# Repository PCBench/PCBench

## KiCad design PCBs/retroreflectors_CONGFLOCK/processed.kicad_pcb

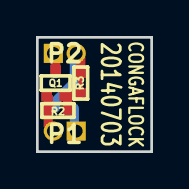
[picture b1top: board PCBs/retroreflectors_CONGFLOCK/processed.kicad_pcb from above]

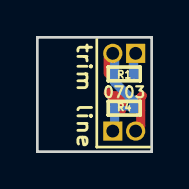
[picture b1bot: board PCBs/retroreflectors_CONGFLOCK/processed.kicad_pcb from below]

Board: 2 copper layers, 6.3 x 6.4 mm, 7 parts (2 on the bottom side), 5 nets.

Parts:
P1: INPUT; GSG-50MIL-HEADER-1x2-TH
P2: ANTENNA; GSG-50MIL-HEADER-1x2-TH
Q1: MOSFET_N; GSG-SOT416-GDS
R1: DNP; GSG-0402
R2: 100k; GSG-0402
R3, R4: 0; GSG-0402-SHORT-10MIL

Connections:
/DRAIN: P2.1, Q1.D, R1.1
/GATE: P1.2, Q1.G, R2.1
/SOURCE: Q1.S, R2.2, R3.2
GND: P2.2, R1.2, R3.1, R4.1
unnamed: P1.1, R4.2

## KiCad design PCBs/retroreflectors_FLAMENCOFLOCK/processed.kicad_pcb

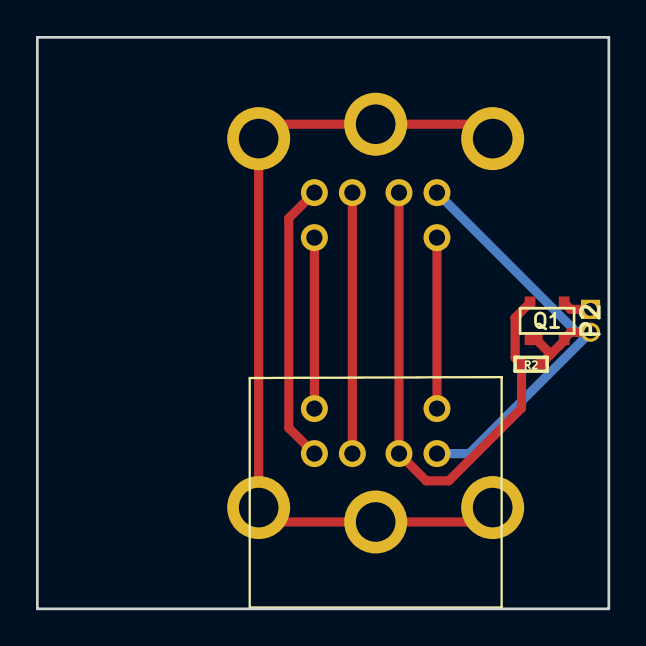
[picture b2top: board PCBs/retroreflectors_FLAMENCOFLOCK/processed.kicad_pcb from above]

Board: 2 copper layers, 31.8 x 31.8 mm, 5 parts (1 on the bottom side), 8 nets.

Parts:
J1, J2: MINIDIN6; GSG-MD-6006
P2: ANTENNA; GSG-50MIL-HEADER-1x2-TH
Q1: MOSFET_N; GSG-SOT143B-GDS
R2: 10k; GSG-0402

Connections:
/DRAIN: P2.1, Q1.D
/GATE: J1.1, J2.1, Q1.G, R2.1
/SHIELD: J1.0, J2.0
GND: J1.3, J2.3, P2.2, Q1.B, Q1.S, R2.2
unnamed: J1.2, J2.2
unnamed: J1.5, J2.5
unnamed: J1.4, J2.4
unnamed: J1.6, J2.6

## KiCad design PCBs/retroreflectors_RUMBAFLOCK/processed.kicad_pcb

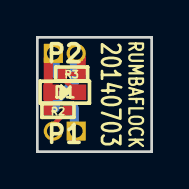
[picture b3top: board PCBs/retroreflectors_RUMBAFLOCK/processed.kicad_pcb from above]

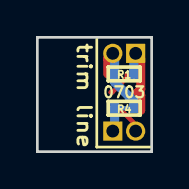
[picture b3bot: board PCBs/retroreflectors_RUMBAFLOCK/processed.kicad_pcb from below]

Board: 2 copper layers, 6.3 x 6.4 mm, 7 parts (2 on the bottom side), 5 nets.

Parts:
D1: PIN; GSG-0603D
P1: INPUT; GSG-50MIL-HEADER-1x2-TH
P2: ANTENNA; GSG-50MIL-HEADER-1x2-TH
R1: DNP; GSG-0402
R2: 10k; GSG-0402
R3, R4: 0; GSG-0402-SHORT-10MIL

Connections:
GND: P2.2, R1.2, R3.1, R4.1
unnamed: P1.1, R4.2
unnamed: P1.2, R2.1
unnamed: D1.2, R3.2
unnamed: D1.1, P2.1, R1.1, R2.2

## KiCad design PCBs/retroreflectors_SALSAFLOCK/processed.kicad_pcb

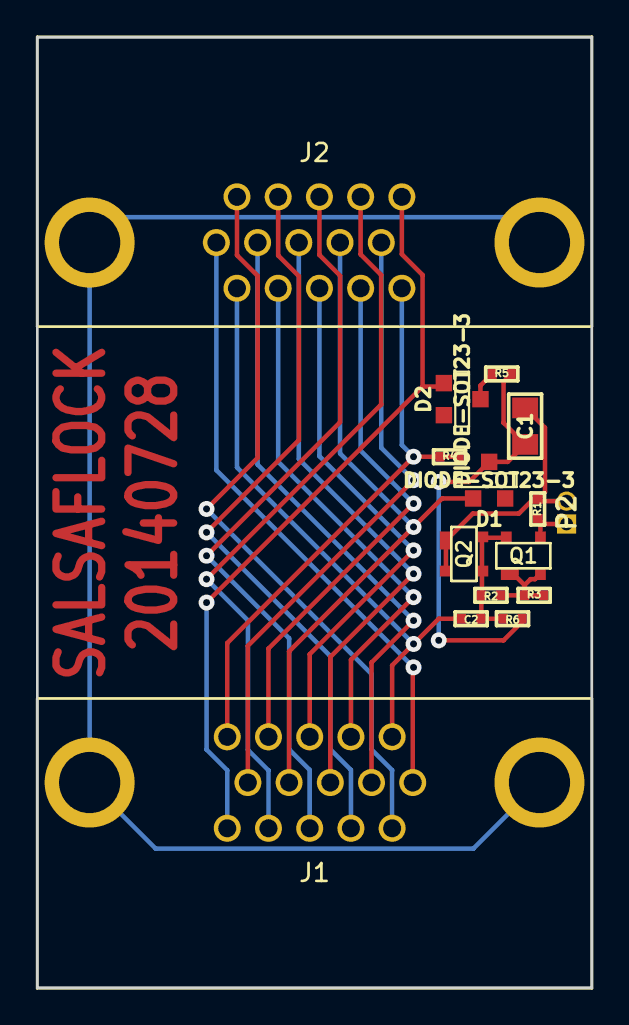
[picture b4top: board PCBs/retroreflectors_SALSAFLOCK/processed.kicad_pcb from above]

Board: 2 copper layers, 30.8 x 52.8 mm, 15 parts (0 on the bottom side), 22 nets.

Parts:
C1: 22uF; GSG-0805
C2: 1uF; GSG-0402
D1, D2: DIODE-SOT23-3; GSG-SOT23-3
J1, J2: DB15-VGA; GSG-DB15-VGA
P2: ANTENNA; GSG-50MIL-HEADER-1x2-TH
Q1, Q2: MOSFET_N; GSG-SOT143B-GDS
R1: DNP; GSG-0402
R2, R5, R6: 10k; GSG-0402
R3, R4: 0; GSG-0402-SHORT-10MIL

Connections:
/DRAIN: P2.1, Q1.D, R1.1
/GATE: C2.2, Q1.G, Q2.D, Q2.G, R2.1, R6.1
/KEY: D1.1, J1.9, J2.9
/RED: C2.1, J1.1, J2.1
/SCL: D2.1, J1.15, J2.15
/SHIELD: J1.0, J2.0
/SOURCE: Q1.B, Q1.S, R2.2, R3.2
/VGAGND: J1.5, J2.5, R4.2
GND: C1.1, P2.2, Q2.B, Q2.S, R1.2
unnamed: J1.10, J2.10
unnamed: J1.7, J2.7
unnamed: J1.2, J2.2
unnamed: J1.3, J2.3
unnamed: J1.4, J2.4
unnamed: J1.6, J2.6
unnamed: J1.8, J2.8
unnamed: J1.11, J2.11
unnamed: J1.12, J2.12
unnamed: J1.13, J2.13
unnamed: J1.14, J2.14
unnamed: D2.3, R5.2
unnamed: C1.2, D1.3, R5.1, R6.2

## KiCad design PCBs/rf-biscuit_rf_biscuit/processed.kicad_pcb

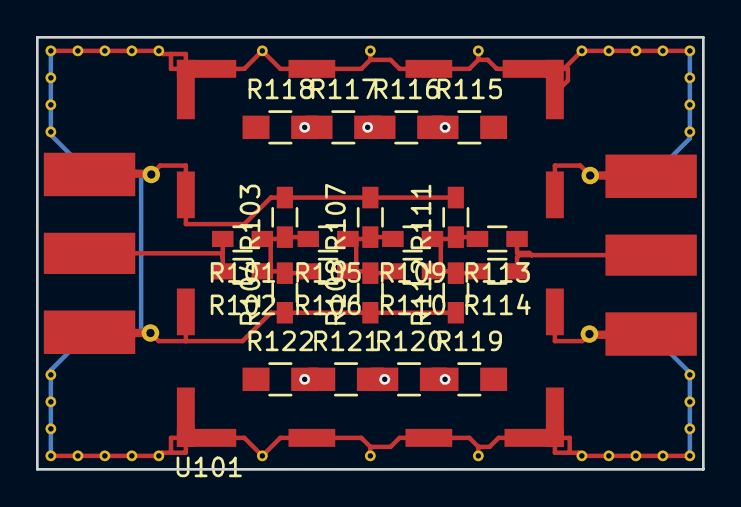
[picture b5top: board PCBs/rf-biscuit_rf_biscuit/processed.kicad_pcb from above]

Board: 2 copper layers, 37.0 x 24.0 mm, 25 parts (0 on the bottom side), 12 nets.

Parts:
P101, P102: BNC; SMA_EDGE_CONNECTOR
R101, R102, R103, R104, R105, R106, R107, R108, R109, R110, R111, R112, R113, R114: R; R_0603_HandSoldering
R115, R116, R117, R118, R119, R120, R121, R122: R; R_0805_HandSoldering
U101: 36103205_HF_Shield; 36103205-HF_Shield

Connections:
GND: P101.2, P102.2, R103.2, R104.1, R107.2, R108.1, R111.2, R112.1, U101.1
unnamed: P101.1, R101.2, R102.2
unnamed: P102.1, R113.1, R114.1
unnamed: R101.1, R102.1, R103.1, R104.2, R105.2, R106.2
unnamed: R105.1, R106.1, R107.1, R108.2, R109.2, R110.2
unnamed: R109.1, R110.1, R111.1, R112.2, R113.2, R114.2
unnamed: R115.1, R116.2
unnamed: R116.1, R117.2
unnamed: R117.1, R118.2
unnamed: R119.1, R120.2
unnamed: R120.1, R121.2
unnamed: R121.1, R122.2

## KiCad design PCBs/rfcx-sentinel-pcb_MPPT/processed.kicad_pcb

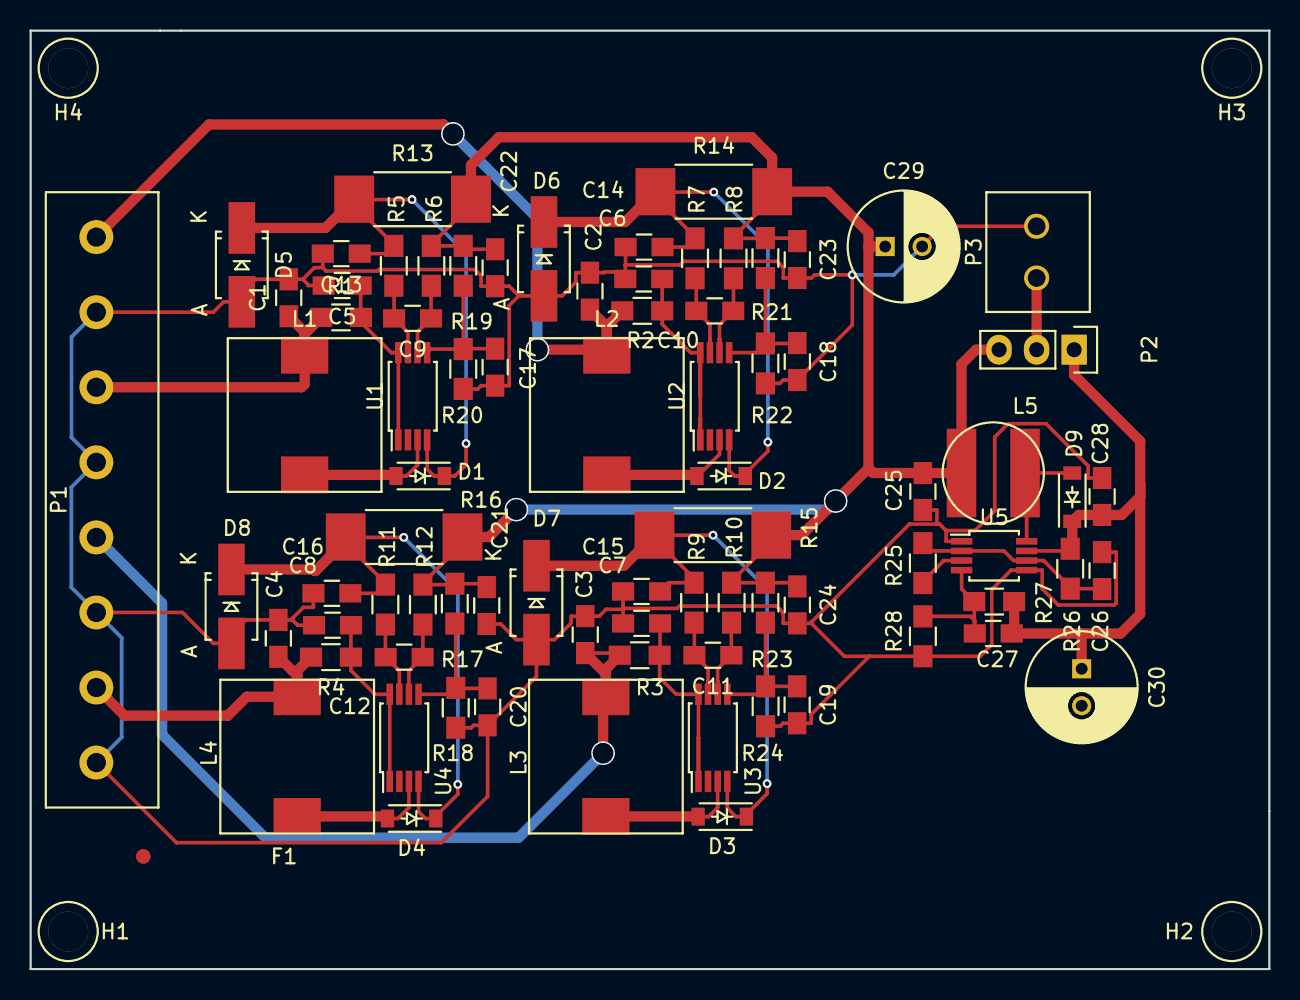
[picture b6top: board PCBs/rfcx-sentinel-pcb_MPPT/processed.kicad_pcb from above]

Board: 2 copper layers, 83.8 x 63.5 mm, 86 parts (1 on the bottom side), 36 nets.

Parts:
C1, C2, C3, C4, C21, C22, C23, C24: 10uF; C_0805_HandSoldering
C5, C6, C7, C8: 100nF; C_0805_HandSoldering
C9, C10, C11, C12, C26: 1uF; C_0805_HandSoldering
C13, C14, C15, C16: 4.7uF; C_0805_HandSoldering
C17, C18, C19, C20: 1nF; C_0805_HandSoldering
C25: 22uF; C_0805_HandSoldering
C27: 39pF; C_0805_HandSoldering
C28: 68uF Tant; C_0805_HandSoldering
C29, C30: DNP; C_Radial_D7.5_L11.2_P2.5
D1, D2, D3, D4: 1n5819; SOD-123
D5, D6, D7, D8: Diode-TVS; Diode-SMA_Handsoldering
D9: 1N5819; SOD-123
F1: Fiducial; Fiducial_1mm_Dia_2.54mm_Outer_CopperTop
H1, H2, H3, H4: Mounting_Hole; Mnt_Hole
L1, L2, L3, L4: 10uH; Ind_10_4x10_4
L5: 6.8uF; Ind_6x6
Noname_1: Symbol_OSHW-Logo_SilkScreen
P1: CONN_01X08; Terminal_Block_8
P2: CONN_01X03; Pin_Header_Straight_1x03
P3: CONN_01X02; TerminalBlock_2
R1, R2, R3, R4, R5, R6, R7, R8, R9, R10, R11, R12: 1k; R_0805_HandSoldering
R13, R14, R15, R16: 0.5, 2W; R_2512_HandSoldering
R17, R19, R21, R23: 330K; R_0805_HandSoldering
R18, R20, R22, R24: 121K; R_0805_HandSoldering
R25: 200K; R_0805_HandSoldering
R26: 49.9; R_0805_HandSoldering
R27: 150K; R_0805_HandSoldering
R28: 49.9K; R_0805_HandSoldering
U1, U2, U3, U4: SPV1040; TSSOP-8_4.4x3mm_Pitch0.65mm
U5: LMR61428; MSOP-8_3x3mm_Pitch0.65mm

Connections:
/LM_FB: C27.1, R27.2, R28.1, U5.4
/MPPT_OUT: C21.1, C22.1, C23.1, C24.1, C25.1, C29.1, L5.1, P2.3, R6.2, R8.2, R10.2, R12.2, R13.2, R14.2, R15.2, R16.2, R17.1, R19.1, R21.1, R23.1
/Panel_Out_V: C27.2, C28.1, C30.1, D9.1, P2.1, R26.1, R27.1, U5.7
GND: C1.2, C2.2, C3.2, C4.2, C5.2, C6.2, C7.2, C8.2, C13.2, C14.2, C15.2, C16.2, C17.2, C18.2, C19.2, C20.2, C21.2, C22.2, C23.2, C24.2, C25.2, C26.2, C28.2, C29.2, D5.2, D6.2, D7.2, D8.2, P1.2, P1.4, P1.6, P1.8, P3.2, R18.2, R20.2, R22.2, R24.2, R28.2, U5.1, U5.5
unnamed: C1.1, L1.1, P1.3, R1.1
unnamed: C2.1, L2.1, P1.1, R2.1
unnamed: C3.1, L3.1, P1.5, R3.1
unnamed: C4.1, L4.1, P1.7, R4.1
unnamed: C5.1, R1.2, U1.1, U1.8
unnamed: C6.1, R2.2, U2.1, U2.8
unnamed: C7.1, R3.2, U3.1, U3.8
unnamed: C8.1, R4.2, U4.1, U4.8
unnamed: C9.1, R6.1, U1.6
unnamed: C9.2, R5.1, U1.7
unnamed: C10.1, R8.1, U2.6
unnamed: C10.2, R7.1, U2.7
unnamed: C11.1, R10.1, U3.6
unnamed: C11.2, R9.1, U3.7
unnamed: C12.1, R12.1, U4.6
unnamed: C12.2, R11.1, U4.7
unnamed: C13.1, D1.1, D5.1, R5.2, R13.1, U1.4
unnamed: C14.1, D2.1, D6.1, R7.2, R14.1, U2.4
unnamed: C15.1, D3.1, D7.1, R9.2, R15.1, U3.4
unnamed: C16.1, D4.1, D8.1, R11.2, R16.1, U4.4
unnamed: C17.1, R19.2, R20.1, U1.5
unnamed: C18.1, R21.2, R22.1, U2.5
unnamed: C19.1, R23.2, R24.1, U3.5
unnamed: C20.1, R17.2, R18.1, U4.5
unnamed: C26.1, R25.1, R26.2, U5.2, U5.6
unnamed: D1.2, L1.2, U1.3
unnamed: D2.2, L2.2, U2.3
unnamed: D3.2, L3.2, U3.3
unnamed: D4.2, L4.2, U4.3
unnamed: D9.2, L5.2, U5.8
unnamed: P2.2, P3.1
unnamed: R25.2, U5.3

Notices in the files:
PCBs/rf-biscuit_rf_biscuit/processed.kicad_pcb:
CC BY-SA 3.0
